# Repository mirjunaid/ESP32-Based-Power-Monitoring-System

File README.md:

# ESP32-Based-Power-Monitoring-System
Power Monitoring system based on esp32 with a OLED display.

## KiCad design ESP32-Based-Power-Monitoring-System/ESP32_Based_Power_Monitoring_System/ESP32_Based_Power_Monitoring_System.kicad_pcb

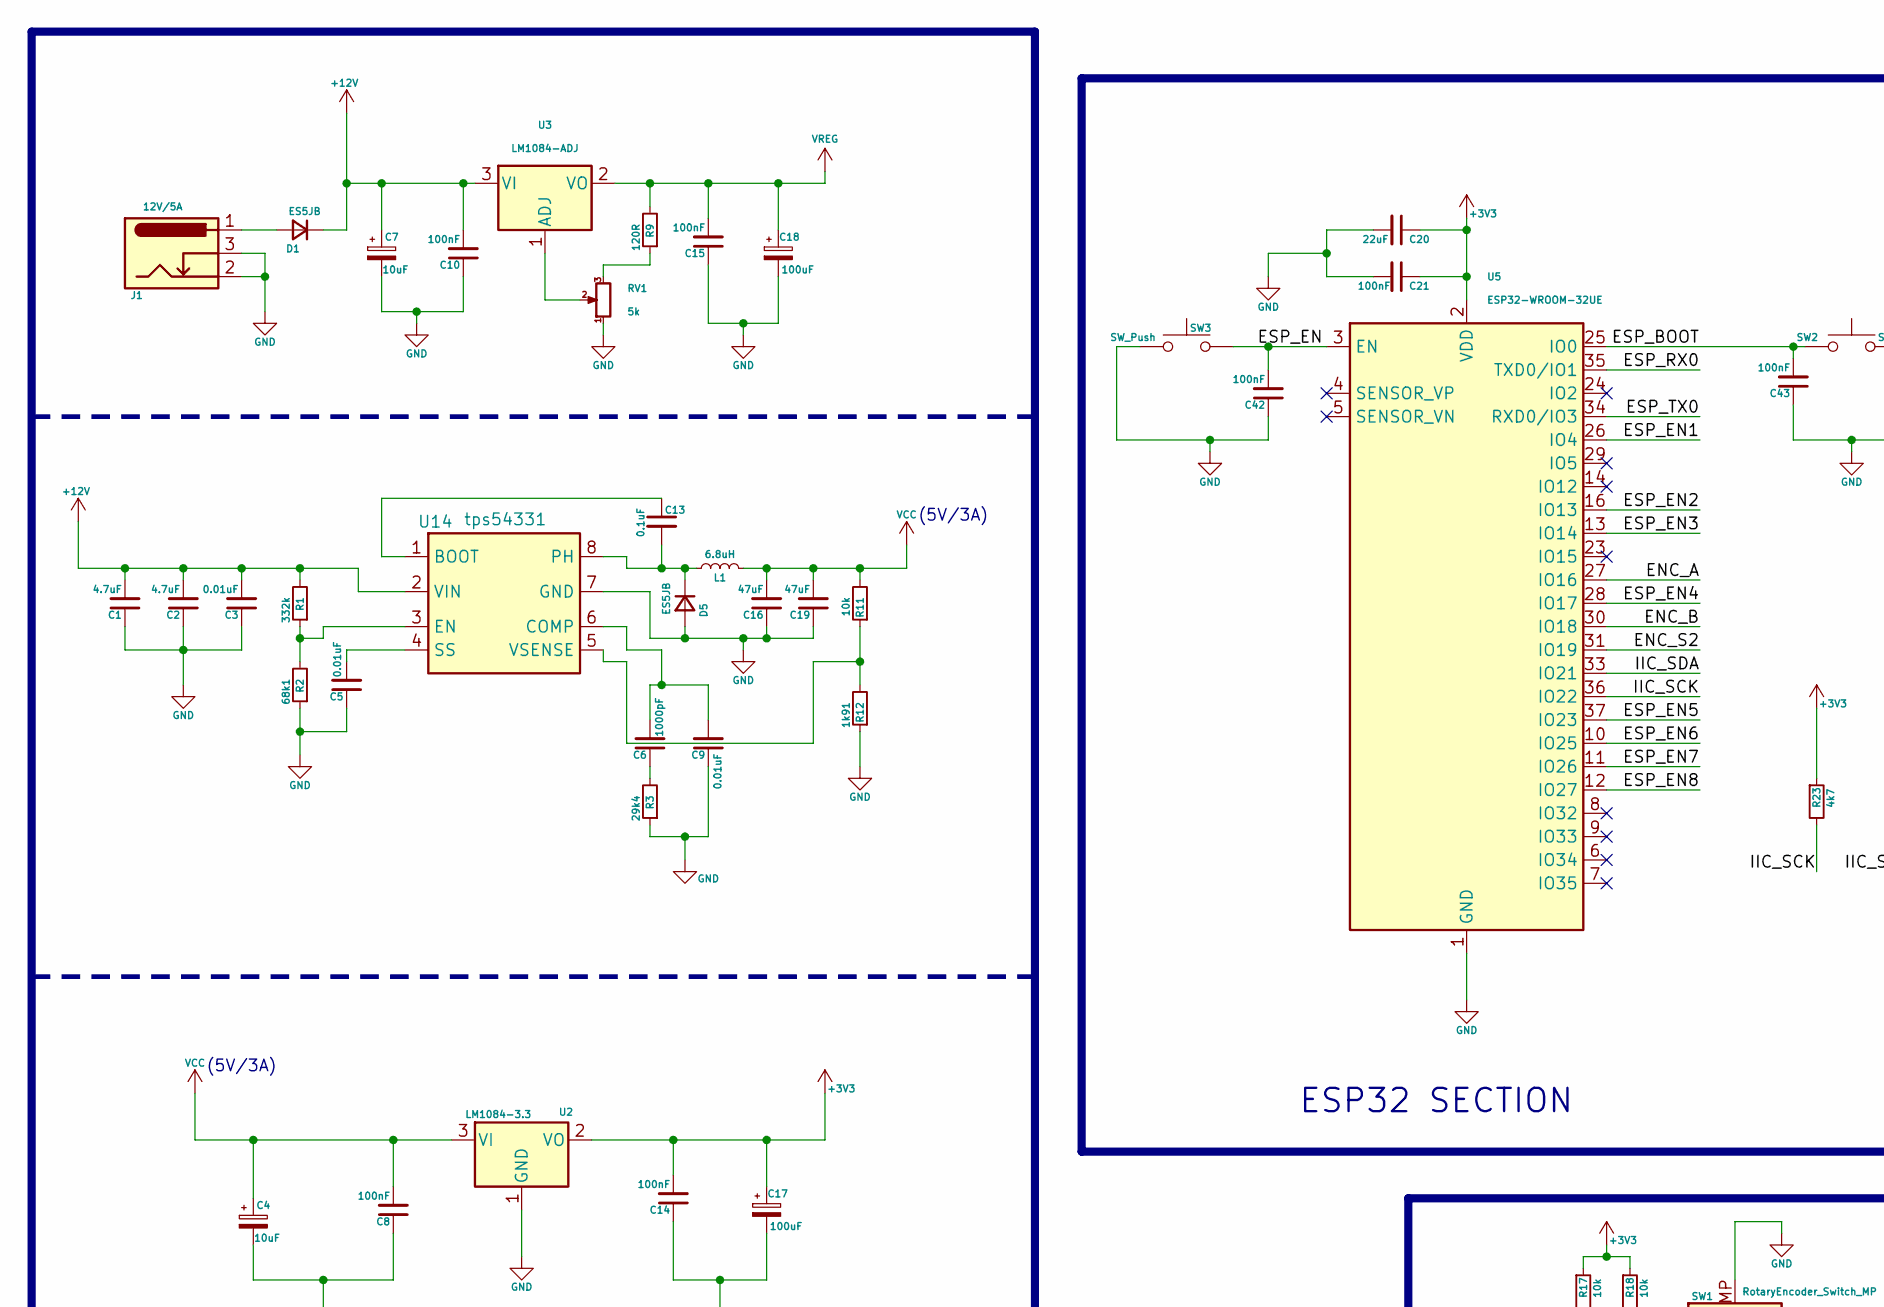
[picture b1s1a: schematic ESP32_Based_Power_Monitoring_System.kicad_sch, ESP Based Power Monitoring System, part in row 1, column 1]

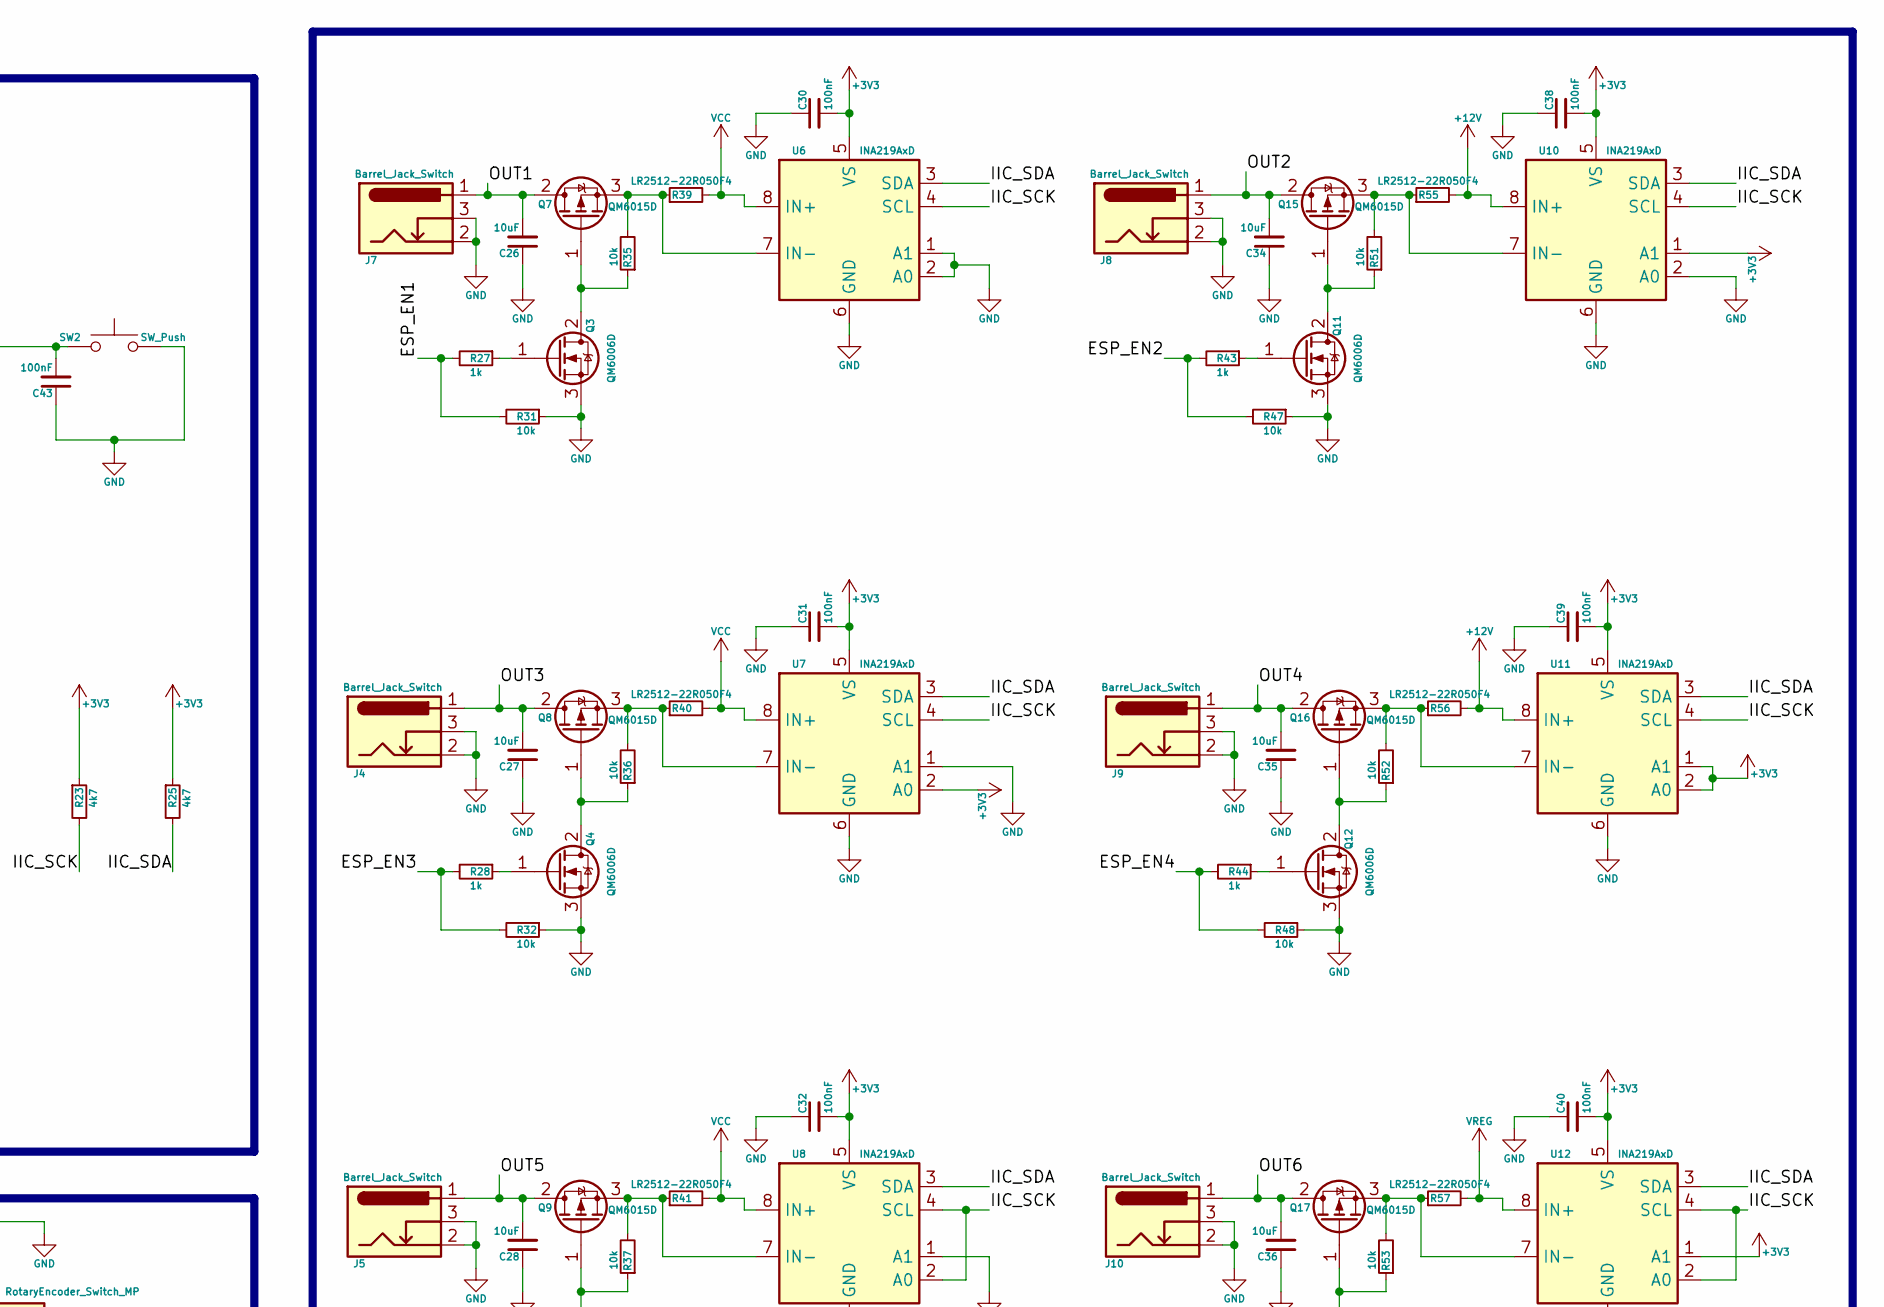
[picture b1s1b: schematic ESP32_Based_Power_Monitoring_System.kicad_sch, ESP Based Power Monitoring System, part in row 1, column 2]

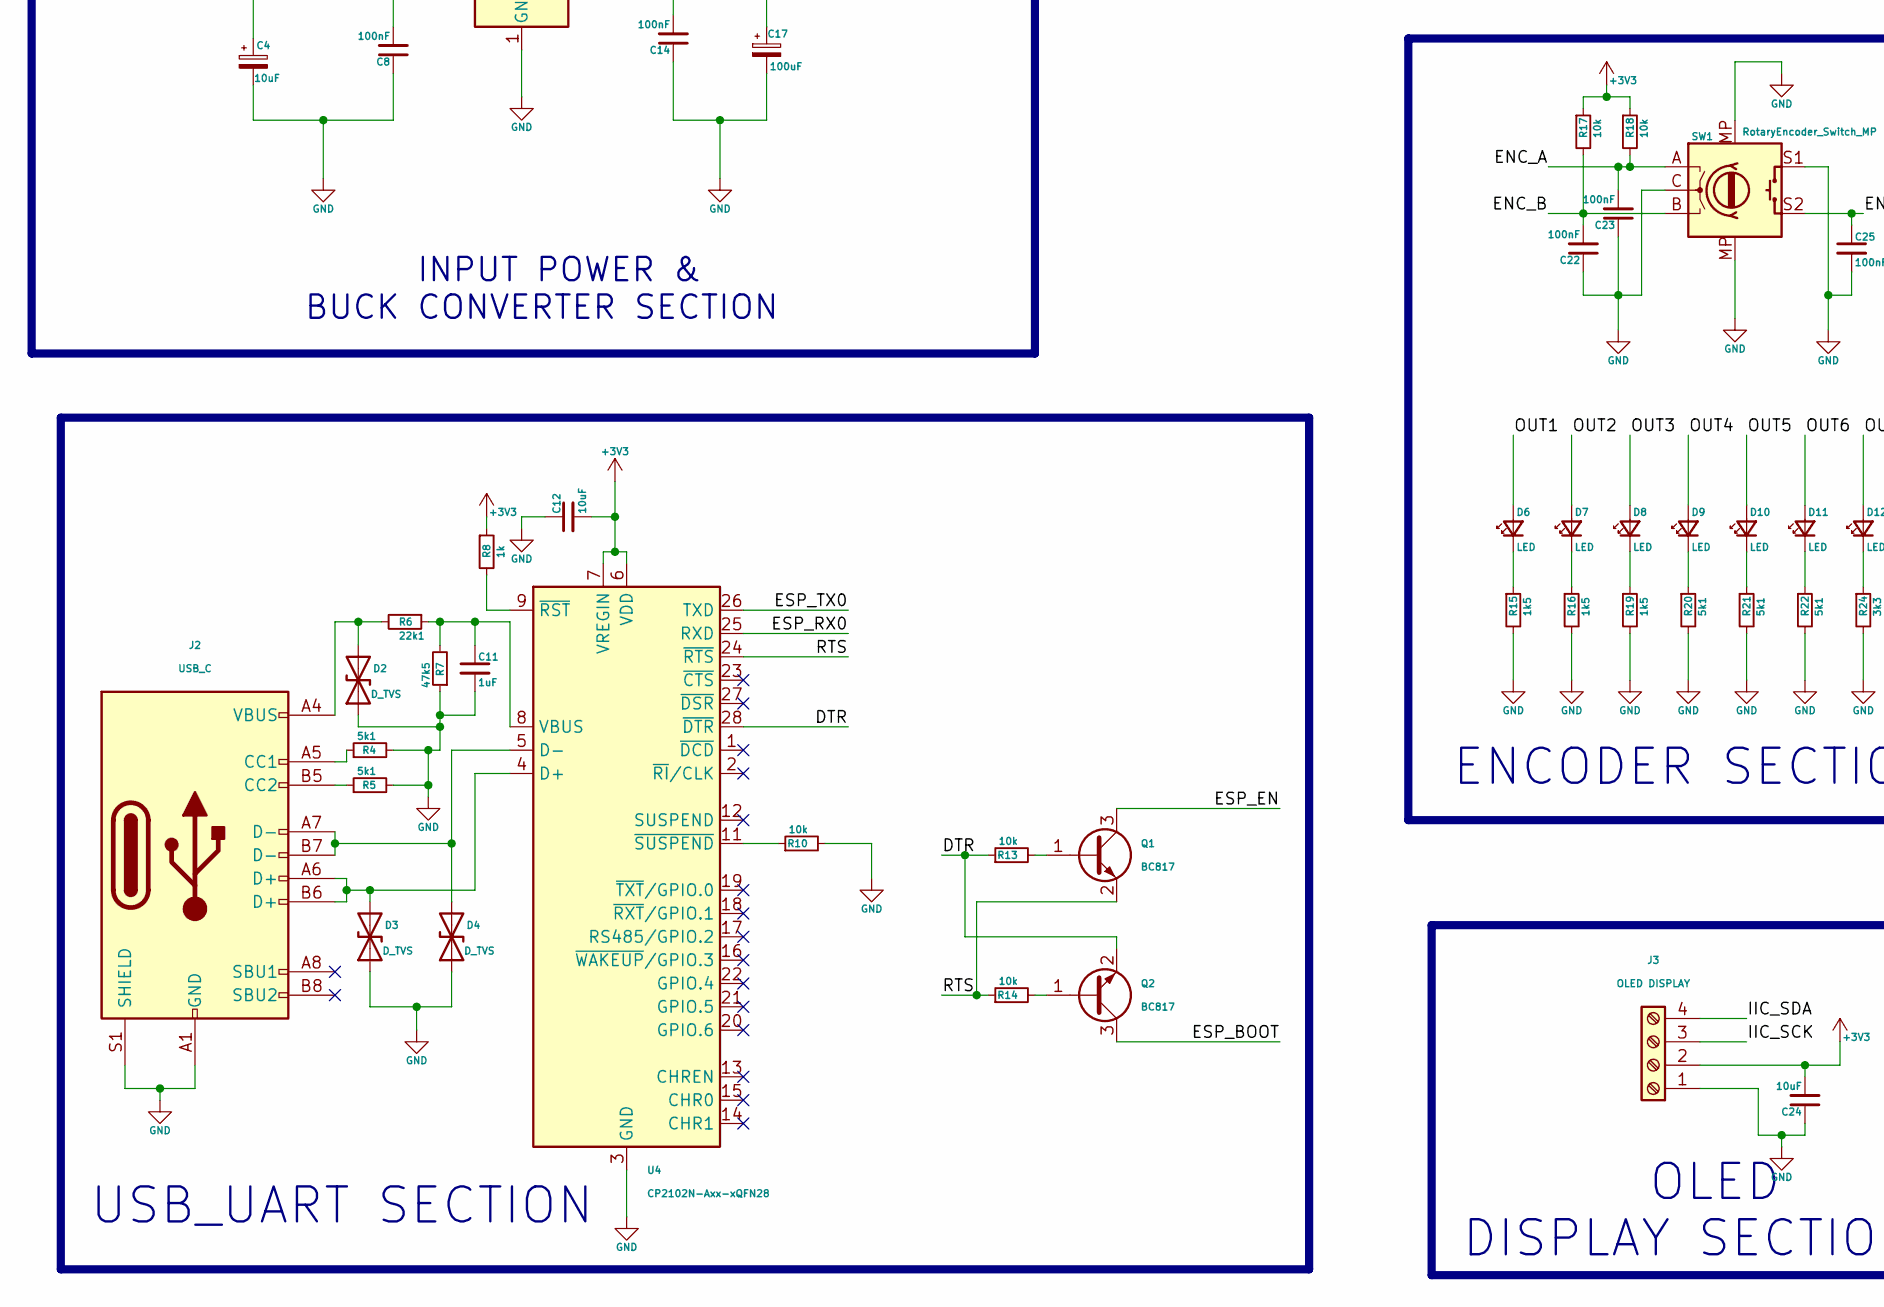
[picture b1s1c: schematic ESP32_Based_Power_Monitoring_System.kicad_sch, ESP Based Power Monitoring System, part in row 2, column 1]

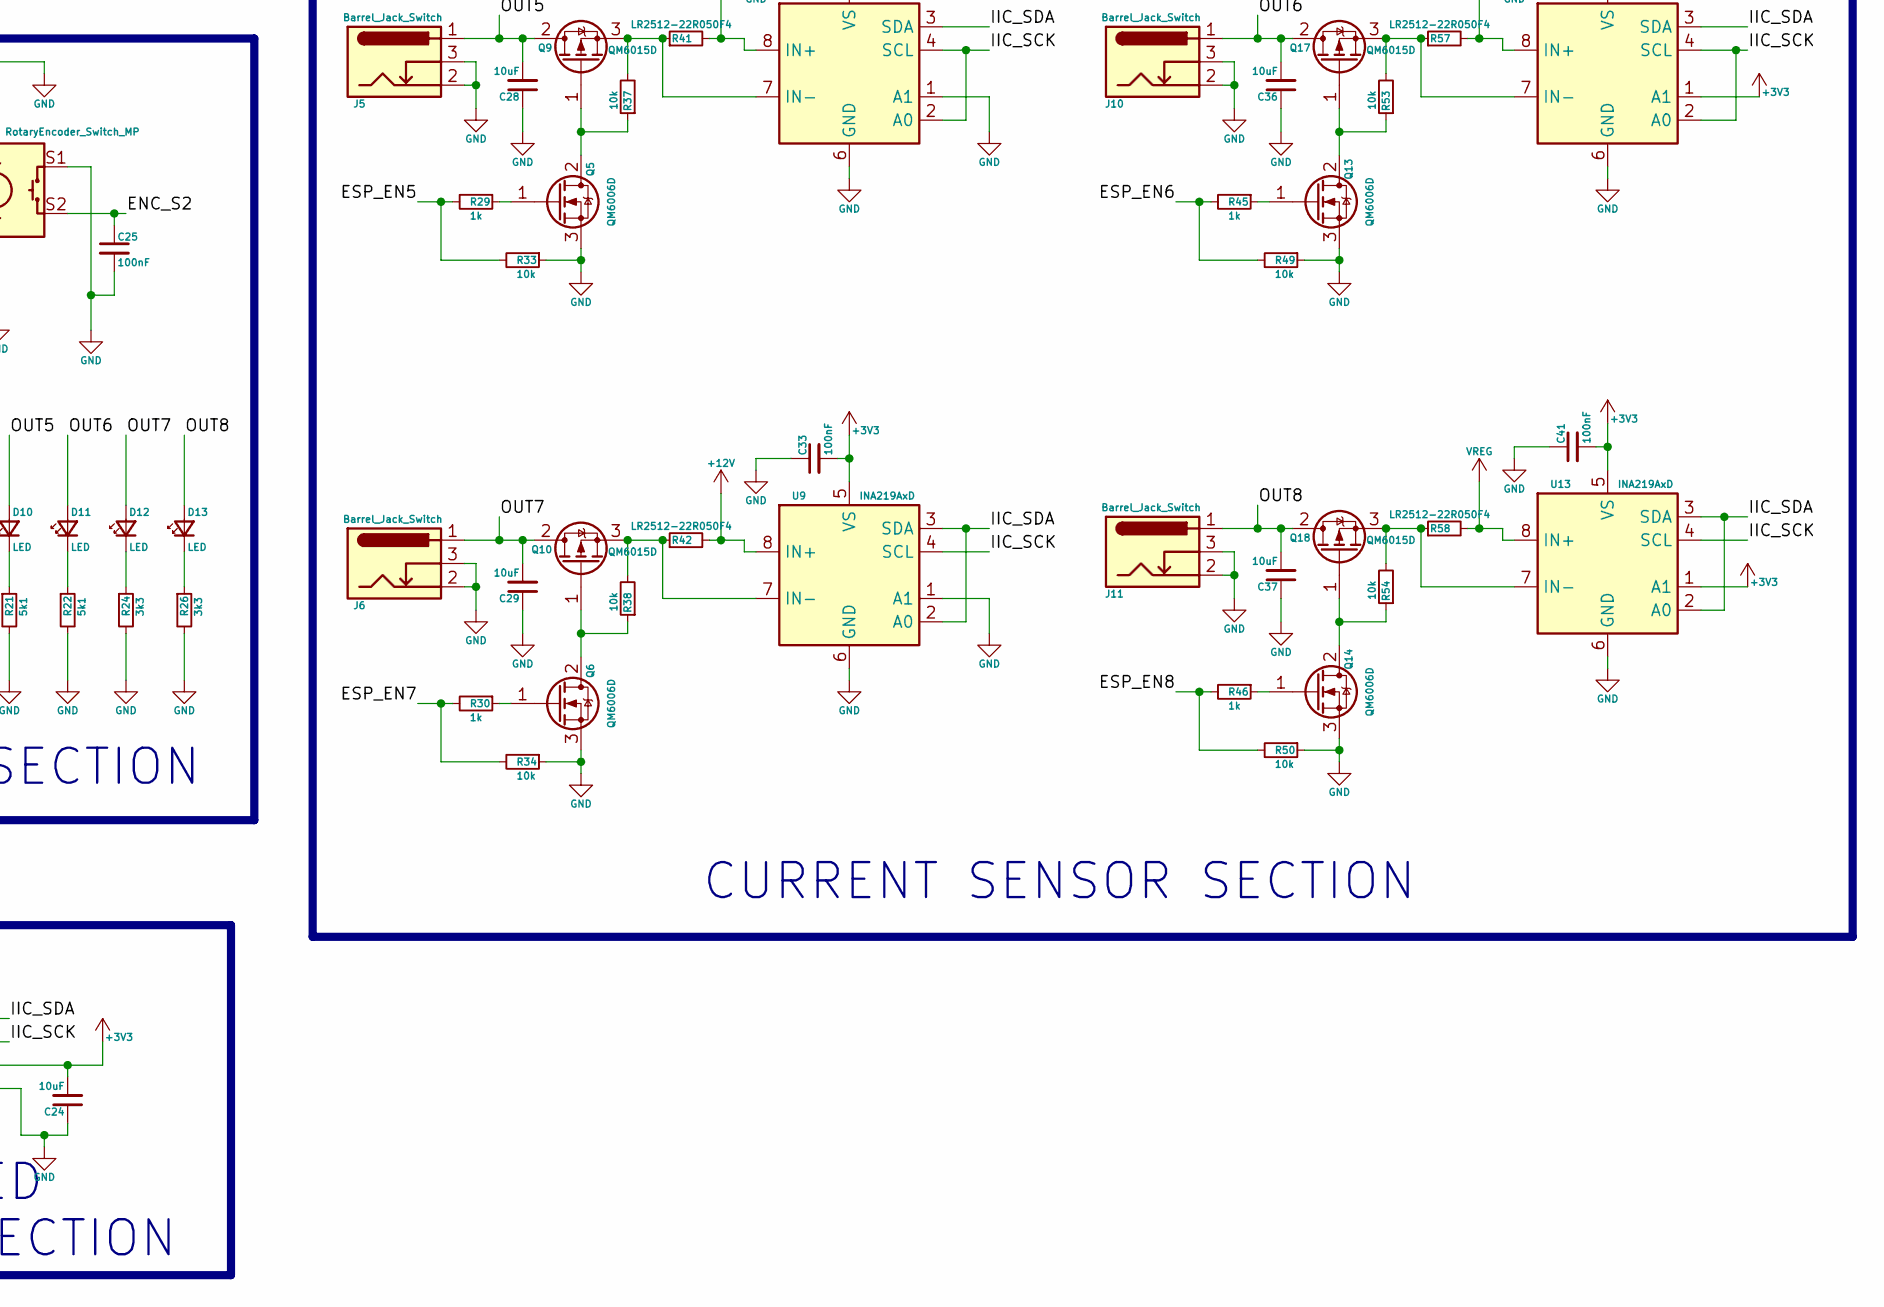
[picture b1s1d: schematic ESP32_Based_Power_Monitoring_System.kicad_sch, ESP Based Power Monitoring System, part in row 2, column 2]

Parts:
C1, C2: 4.7uF; C_0603_1608Metric
C3, C5, C9: 0.01uF; C_0603_1608Metric
C4, C7, C12, C24, C26, C27, C28, C29, C34, C35, C36, C37: 10uF; C_0603_1608Metric
C6: 1000pF; C_0603_1608Metric
C8, C10, C14, C15, C21, C22, C23, C25, C30, C31, C32, C33, C38, C39, C40, C41, C42, C43: 100nF; C_0603_1608Metric
C11: 1uF; C_0603_1608Metric
C13: 0.1uF; C_0603_1608Metric
C16, C19: 47uF; C_0603_1608Metric
C17, C18: 100uF; C_0603_1608Metric
C20: 22uF; C_0603_1608Metric
D1, D5: ES5JB; D_SMA
D2, D3, D4: D_TVS; D_SOD-523
D6, D7, D8, D9, D10, D11, D12, D13: LED; LED_0603_1608Metric
J1: 12V/5A; BarrelJack_Horizontal
J2: USB_C; USB_C_Receptacle_HCTL_HC-TYPE-C-16P-01A
J3: OLED DISPLAY; PinHeader_1x04_P2.54mm_Vertical
J4, J5, J6, J7, J8, J9, J10, J11: Barrel_Jack_Switch; BarrelJack_Horizontal
L1: 6.8uH; L_Sunlord_MWSA0412S
Q1, Q2: BC817; SOT-23
Q3, Q4, Q5, Q6, Q11, Q12, Q13, Q14: QM6006D; SOT-23
Q7, Q8, Q9, Q10, Q15, Q16, Q17, Q18: QM6015D; SOT-23
R1: 332k; R_0603_1608Metric
R2: 68k1; R_0603_1608Metric
R3: 29k4; R_0603_1608Metric
R4, R5, R20, R21, R22: 5k1; R_0603_1608Metric
R6: 22k1; R_0603_1608Metric
R7: 47k5; R_0603_1608Metric
R8, R27, R28, R29, R30, R43, R44, R45, R46: 1k; R_0603_1608Metric
R9: 120R; R_0603_1608Metric
R10, R11, R13, R14, R17, R18, R31, R32, R33, R34, R35, R36, R37, R38, R47, R48, R49, R50, R51, R52, R53, R54: 10k; R_0603_1608Metric
R12: 1k91; R_0603_1608Metric
R15, R16, R19: 1k5; R_0603_1608Metric
R23, R25: 4k7; R_0603_1608Metric
R24, R26: 3k3; R_0603_1608Metric
R39, R40, R41, R42, R55, R56, R57, R58: LR2512-22R050F4; R_2512_6332Metric
RV1: 5k; Potentiometer_ACP_CA6-VSMD_Vertical
SW1: RotaryEncoder_Switch_MP; RotaryEncoder_Alps_EC12E-Switch_Vertical_H20mm
SW2, SW3: SW_Push; SW_SPST_TS-1088-xR020
U2: LM1084-3.3; TO-263-2
U3: LM1084-ADJ; TO-263-2
U4: CP2102N-Axx-xQFN28; QFN-28-1EP_5x5mm_P0.5mm_EP3.35x3.35mm
U5: ESP32-WROOM-32UE
U6, U7, U8, U9, U10, U11, U12, U13: INA219AxD; SOIC-8_3.9x4.9mm_P1.27mm
U14: tps54331; SO-8_3.9x4.9mm_P1.27mm

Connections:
+3V3: C12.2, C14.2, C17.1, C20.1, C21.1, C24.2, C30.2, C31.2, C32.2, C33.2, C38.2, C39.2, C40.2, C41.2, J3.2, R8.1, R17.1, R18.1, R23.1, R25.1, U2.2 (VO), U4.6 (VDD), U4.7 (VREGIN), U5.2 (VDD), U6.5 (VS), U7.2 (A0), U7.5 (VS), U8.5 (VS), U9.5 (VS), U10.1 (A1), U10.5 (VS), U11.1 (A1), U11.2 (A0), U11.5 (VS), U12.1 (A1), U12.5 (VS), U13.1 (A1), U13.5 (VS)
+12V: C1.2, C2.2, C3.2, C7.1, C10.2, D1.1 (K), R1.2, R42.2, R55.2, R56.2, U3.3 (VI), U9.8 (IN+), U10.8 (IN+), U11.8 (IN+), U14.2 (VIN)
/DTR: Q2.2 (C), R13.1, U4.28 (~DTR)
/ENC_A: C23.2, R18.2, SW1.A, U5.27 (IO16)
/ENC_B: C22.2, R17.2, SW1.B, U5.30 (IO18)
/ENC_S2: C25.1, SW1.S2, U5.31 (IO19)
/ESP_BOOT: C43.2, Q2.3 (E), SW2.1, U5.25 (IO0)
/ESP_EN: C42.2, Q1.3 (C), SW3.2, U5.3 (EN)
/ESP_EN1: R27.2, R31.2, U5.26 (IO4)
/ESP_EN2: R43.2, R47.2, U5.16 (IO13)
/ESP_EN3: R28.2, R32.2, U5.13 (IO14)
/ESP_EN4: R44.2, R48.2, U5.28 (IO17)
/ESP_EN5: R29.2, R33.2, U5.37 (IO23)
/ESP_EN6: R45.2, R49.2, U5.10 (IO25)
/ESP_EN7: R30.2, R34.2, U5.11 (IO26)
/ESP_EN8: R46.2, R50.2, U5.12 (IO27)
/ESP_RX0: U4.25 (RXD), U5.35 (TXD0/IO1)
/ESP_TX0: U4.26 (TXD), U5.34 (RXD0/IO3)
/IIC_SCK: J3.3, R23.2, U5.36 (IO22), U6.4 (SCL), U7.4 (SCL), U8.2 (A0), U8.4 (SCL), U9.4 (SCL), U10.4 (SCL), U11.4 (SCL), U12.2 (A0), U12.4 (SCL), U13.4 (SCL)
/IIC_SDA: J3.4, R25.2, U5.33 (IO21), U6.3 (SDA), U7.3 (SDA), U8.3 (SDA), U9.2 (A0), U9.3 (SDA), U10.3 (SDA), U11.3 (SDA), U12.3 (SDA), U13.2 (A0), U13.3 (SDA)
/OUT1: C26.2, D6.2 (A), J7.1, Q7.2 (D)
/OUT2: C34.2, D7.2 (A), J8.1, Q15.2 (D)
/OUT3: C27.2, D8.2 (A), J4.1, Q8.2 (D)
/OUT4: C35.2, D9.2 (A), J9.1, Q16.2 (D)
/OUT5: C28.2, D10.2 (A), J5.1, Q9.2 (D)
/OUT6: C36.2, D11.2 (A), J10.1, Q17.2 (D)
/OUT7: C29.2, D12.2 (A), J6.1, Q10.2 (D)
/OUT8: C37.2, D13.2 (A), J11.1, Q18.2 (D)
/RTS: Q1.2 (E), R14.1, U4.24 (~RTS)
GND: C1.1, C2.1, C3.1, C4.2, C5.1, C7.2, C8.1, C9.1, C10.1, C11.2, C12.1, C14.1, C15.1, C16.1, C17.2, C18.2, C19.1, C20.2, C21.2, C22.1, C23.1, C24.1, C25.2, C26.1, C27.1, C28.1, C29.1, C30.1, C31.1, C32.1, C33.1, C34.1, C35.1, C36.1, C37.1, C38.1, C39.1, C40.1, C41.1, C42.1, C43.1, D2.1 (A1), D3.1 (A1), D4.1 (A1), D5.2 (A), J1.2, J1.3, J2.A1 (GND), J2.A12 (GND), J2.B1 (GND), J2.B12 (GND), J2.S1 (SHIELD), J3.1, J4.2, J4.3, J5.2, J5.3, J6.2, J6.3, J7.2, J7.3, J8.2, J8.3, J9.2, J9.3, J10.2, J10.3, J11.2, J11.3, Q3.3 (S), Q4.3 (S), Q5.3 (S), Q6.3 (S), Q11.3 (S), Q12.3 (S), Q13.3 (S), Q14.3 (S), R2.1, R3.1, R4.2, R5.2, R7.1, R10.2, R12.1, R15.2, R16.2, R19.2, R20.2, R21.2, R22.2, R24.2, R26.2, R31.1, R32.1, R33.1, R34.1, R47.1, R48.1, R49.1, R50.1, RV1.1, SW1.C, SW1.MP, SW1.S1, SW2.2, SW3.1, U2.1 (GND), U4.3 (GND), U4.29 (GND), U5.1 (GND), U5.15 (GND), U5.38 (GND), U5.39 (GND), U6.1 (A1), U6.2 (A0), U6.6 (GND), U7.1 (A1), U7.6 (GND), U8.1 (A1), U8.6 (GND), U9.1 (A1), U9.6 (GND), U10.2 (A0), U10.6 (GND), U11.6 (GND), U12.6 (GND), U13.6 (GND), U14.7 (GND)
unnamed: C6.1, R3.2
unnamed: D1.2 (A), J1.1
unnamed: D2.2 (A2), J2.A4 (VBUS), J2.A9 (VBUS), J2.B4 (VBUS), J2.B9 (VBUS), R6.2
unnamed: D3.2 (A2), J2.A6 (D+), J2.B6 (D+), U4.4 (D+)
unnamed: D4.2 (A2), J2.A7 (D-), J2.B7 (D-), U4.5 (D-)
unnamed: C13.2, D5.1 (K), L1.1, U14.8 (PH)
unnamed: D6.1 (K), R15.1
unnamed: D7.1 (K), R16.1
unnamed: D8.1 (K), R19.1
unnamed: D9.1 (K), R20.1
unnamed: D10.1 (K), R21.1
unnamed: D11.1 (K), R22.1
unnamed: D12.1 (K), R24.1
unnamed: D13.1 (K), R26.1
unnamed: J2.A5 (CC1), R4.1
unnamed: J2.B5 (CC2), R5.1
unnamed: Q1.1 (B), R13.2
unnamed: Q2.1 (B), R14.2
unnamed: Q3.2 (D), Q7.1 (G), R35.1
unnamed: Q3.1 (G), R27.1
unnamed: Q4.2 (D), Q8.1 (G), R36.1
unnamed: Q4.1 (G), R28.1
unnamed: Q5.2 (D), Q9.1 (G), R37.1
unnamed: Q5.1 (G), R29.1
unnamed: Q6.1 (G), R30.1
unnamed: Q7.3 (S), R35.2, R39.1, U6.7 (IN-)
unnamed: Q8.3 (S), R36.2, R40.1, U7.7 (IN-)
unnamed: Q9.3 (S), R37.2, R41.1, U8.7 (IN-)
unnamed: Q6.2 (D), Q10.1 (G), R38.1
unnamed: Q10.3 (S), R38.2, R42.1, U9.7 (IN-)
unnamed: Q11.2 (D), Q15.1 (G), R51.1
unnamed: Q11.1 (G), R43.1
unnamed: Q12.2 (D), Q16.1 (G), R52.1
unnamed: Q12.1 (G), R44.1
unnamed: Q13.2 (D), Q17.1 (G), R53.1
unnamed: Q13.1 (G), R45.1
unnamed: Q14.2 (D), Q18.1 (G), R54.1
unnamed: Q14.1 (G), R46.1
unnamed: Q15.3 (S), R51.2, R55.1, U10.7 (IN-)
unnamed: Q16.3 (S), R52.2, R56.1, U11.7 (IN-)
unnamed: Q17.3 (S), R53.2, R57.1, U12.7 (IN-)
unnamed: Q18.3 (S), R54.2, R58.1, U13.7 (IN-)
unnamed: R9.1, RV1.3
unnamed: RV1.2, U3.1 (ADJ)
unnamed: C11.1, R6.1, R7.2, U4.8 (VBUS)
unnamed: R8.2, U4.9 (~RST)
unnamed: R10.1, U4.11 (~SUSPEND)
unnamed: C13.1, U14.1 (BOOT)
unnamed: C6.2, C9.2, U14.6 (COMP)
unnamed: R1.1, R2.2, U14.3 (EN)
unnamed: C5.2, U14.4 (SS)
unnamed: R11.1, R12.2, U14.5 (VSENSE)
VCC: C4.1, C8.2, C16.2, C19.2, L1.2, R11.2, R39.2, R40.2, R41.2, U2.3 (VI), U6.8 (IN+), U7.8 (IN+), U8.8 (IN+)
VREG: C15.2, C18.1, R9.2, R57.2, R58.2, U3.2 (VO), U12.8 (IN+), U13.8 (IN+)

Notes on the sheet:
INPUT POWER & BUCK CONVERTER SECTION
ENCODER SECTION
USB_UART SECTION
OLED DISPLAY SECTION
CURRENT SENSOR SECTION
ESP32 SECTION
(5V/3A)

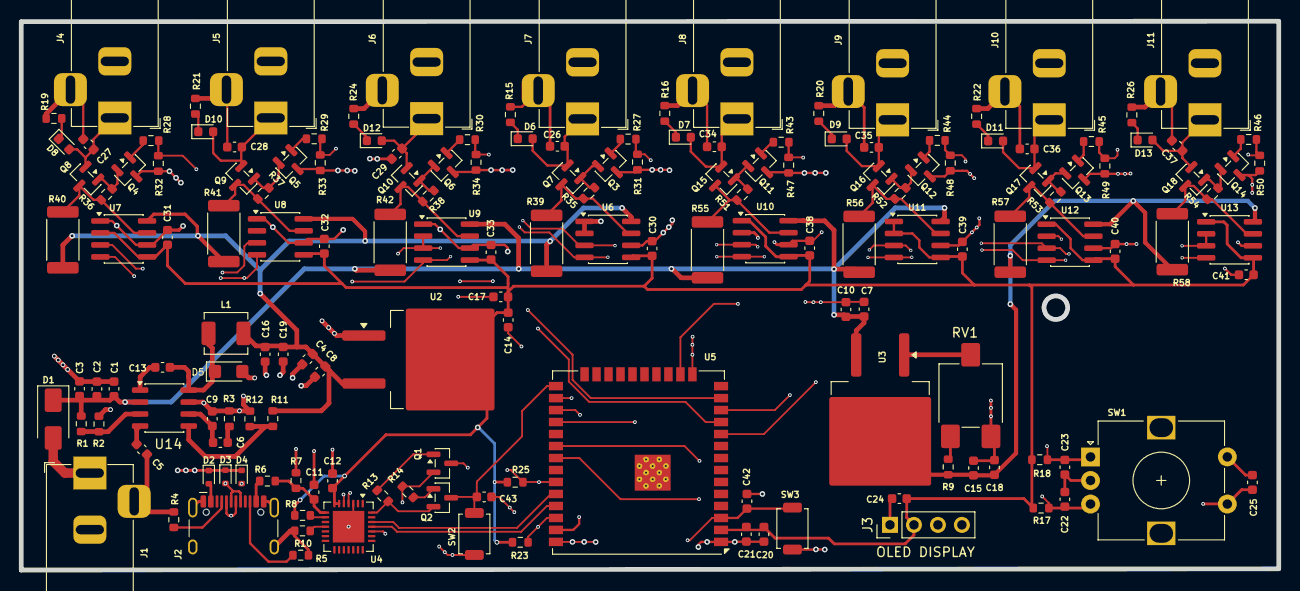
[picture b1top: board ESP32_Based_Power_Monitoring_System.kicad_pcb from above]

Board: 4 copper layers, 133.3 x 58.2 mm, 161 parts (0 on the bottom side), 84 nets.
